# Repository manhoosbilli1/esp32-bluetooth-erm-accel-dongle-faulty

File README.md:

# daronjli_dongle_final_manufactured

ESP32 Bluetooth dongle with ERM haptic motor and accelerometer - FAULTY: wrong ORing circuit, used NMOS instead of PMOS

## At a Glance

- **Status**: Manufactured
- **Board size**: 23.26 x 28.39 mm
- **Layers**: 4
- **Components**: 56
- **Key ICs**:
  - U1: MCP73831-2-MC
  - U2: CP2102N-Axx-xQFN24
  - U3: LIS3DH
  - U4: DRV2605LDGS
  - U5: SY8089AAAC
  - U6: ESP32-WROOM-32E

## Schematic

Full PDF: [reports/schematic.pdf](reports/schematic.pdf)

## Component Roles

- **ESP32-WROVER-E** - main MCU with Bluetooth; firmware runs here
- **DRV2605LDGS** - haptic motor driver (configured for ERM motor) for tactile feedback
- **LIS3DH** - 3-axis accelerometer for orientation / motion detection
- **CP2102N** - USB-to-UART bridge for firmware programming
- **TPS63020** - buck-boost regulator (stable 3.3 V from a swinging LiPo)
- **MCP73871** - LiPo charger with PowerPath (USB vs battery source switching)
- **MAX17048** - I2C fuel gauge for battery percentage

## Known fault

This manufactured revision has a **broken OR-ing / PowerPath circuit**: the design used an N-channel MOSFET where a P-channel MOSFET was required. Result: source switching between USB and battery does not work correctly. Use the active [daronjli-dongle](https://github.com/manhoosbilli1/daronjli-dongle) repo for the fix.

## PCB

**Top copper**

**Bottom copper**

## Bill of Materials

| Refs | Value | Footprint | Qty | MPN | LCSC |
|------|-------|-----------|----:|-----|------|
| C1,C3,C7,C14-C16 | 100nF | Capacitor_SMD:C_0402_1005Metric | 6 |  |  |
| C2,C6 | 4.7uF | Capacitor_SMD:C_0402_1005Metric | 2 |  | [C307423](https://www.lcsc.com/product-detail/_C307423.html) |
| C4,C5 | 22uF | Capacitor_SMD:C_0402_1005Metric | 2 |  |  |
| C8,C10,C13 | 10uF | Capacitor_SMD:C_0402_1005Metric | 3 |  |  |
| C9,C12 | 1uF | Capacitor_SMD:C_0402_1005Metric | 2 |  |  |
| C11 | 22pF | Capacitor_SMD:C_0402_1005Metric | 1 |  |  |
| D1 | WS2812B | PCM_JLCPCB:LED_WS2812B_PLCC4_5.0x5.0mm_P3.2mm | 1 |  | [C22461793](https://www.lcsc.com/product-detail/_C22461793.html) |
| D2,D5,D6 | H5VL06B | PCM_JLCPCB:D_DFN0603-2L | 3 |  | [C7420373](https://www.lcsc.com/product-detail/_C7420373.html) |
| D3 | Red | PCM_JLCPCB:D_0603 | 1 |  | [C2286](https://www.lcsc.com/product-detail/_C2286.html) |
| D4 | B5819W | Diode_SMD:D_SOD-123 | 1 |  |  |
| L1 | 2.2uH | Inductor_SMD:L_1008_2520Metric_Pad1.43x2.20mm_HandSolder | 1 |  |  |
| Q1,Q2 | BC817 | Package_TO_SOT_SMD:SOT-23 | 2 |  |  |
| Q3 | DMG3414U | Package_TO_SOT_SMD:SOT-23 | 1 |  |  |
| R1-R3,R11,R14,R15 | 10k | Resistor_SMD:R_0402_1005Metric | 6 |  | [C60490](https://www.lcsc.com/product-detail/_C60490.html) |
| R4 | 1k | Resistor_SMD:R_0402_1005Metric | 1 |  | [C106235](https://www.lcsc.com/product-detail/_C106235.html) |
| R5,R13 | 5.1kΩ | PCM_JLCPCB:R_0402 | 2 |  | [C25905](https://www.lcsc.com/product-detail/_C25905.html) |
| R6-R8 | 2.2k | Resistor_SMD:R_0402_1005Metric | 3 |  |  |
| R9,R18 | 100k | Resistor_SMD:R_0402_1005Metric | 2 |  |  |
| R10 | 22.1k | Resistor_SMD:R_0402_1005Metric | 1 |  | [C43473](https://www.lcsc.com/product-detail/_C43473.html) |
| R12 | 10kΩ | PCM_JLCPCB:R_0402 | 1 |  | [C25744](https://www.lcsc.com/product-detail/_C25744.html) |
| R16 | 4.7kΩ | PCM_JLCPCB:R_0402 | 1 |  | [C25900](https://www.lcsc.com/product-detail/_C25900.html) |
| TP1-TP4 | TestPoint | TestPoint:TestPoint_Pad_3.0x3.0mm | 4 |  |  |
| TP5,TP6 | TestPoint | TestPoint:TestPoint_Pad_D1.0mm | 2 |  |  |
| U1 | MCP73831-2-MC | Package_DFN_QFN:DFN-8-1EP_3x2mm_P0.5mm_EP1.7x1.4mm | 1 |  | [C150772](https://www.lcsc.com/product-detail/_C150772.html) |
| U2 | CP2102N-Axx-xQFN24 | Package_DFN_QFN:QFN-24-1EP_4x4mm_P0.5mm_EP2.6x2.6mm | 1 |  | [C969151](https://www.lcsc.com/product-detail/_C969151.html) |
| U3 | LIS3DH | Package_LGA:LGA-16_3x3mm_P0.5mm_LayoutBorder3x5y | 1 |  |  |
| U4 | DRV2605LDGS | Package_SO:VSSOP-10_3x3mm_P0.5mm | 1 |  |  |
| U5 | SY8089AAAC | footprints:SY8089AAAC_SGY | 1 |  |  |
| U6 | ESP32-WROOM-32E | RF_Module:ESP32-WROOM-32D | 1 |  | [C701343](https://www.lcsc.com/product-detail/_C701343.html) |
| USB1 | HX-TYPE-C 16P 180 LC-B H10.0 TYPE C VERTICAL | :USB-C-TH_HX-TYPE-C-16P-180-LC-BH10.0-TYPE-C-VERTICAL | 1 |  |  |

_17 of 30 line items don't have an LCSC code in the schematic - search [LCSC](https://www.lcsc.com/) or [JLC parts search](https://jlcsearch.tscircuit.com/) by MPN or footprint when sourcing._

## Files

- `daronjli_dongle.kicad_pro` - KiCad project
- `daronjli_dongle.kicad_sch` - schematic source
- `daronjli_dongle.kicad_pcb` - PCB layout source
- `reports/schematic.pdf` - full schematic (printable)
- `reports/bom.csv` - bill of materials
- `reports/pcb-top.svg`, `reports/pcb-bottom.svg` - copper artwork
- `reports/board-stats.json` - KiCad-generated board statistics

---

_Renders and metadata auto-generated by `Backup-KiCadProject.ps1` using KiCad 10.0._

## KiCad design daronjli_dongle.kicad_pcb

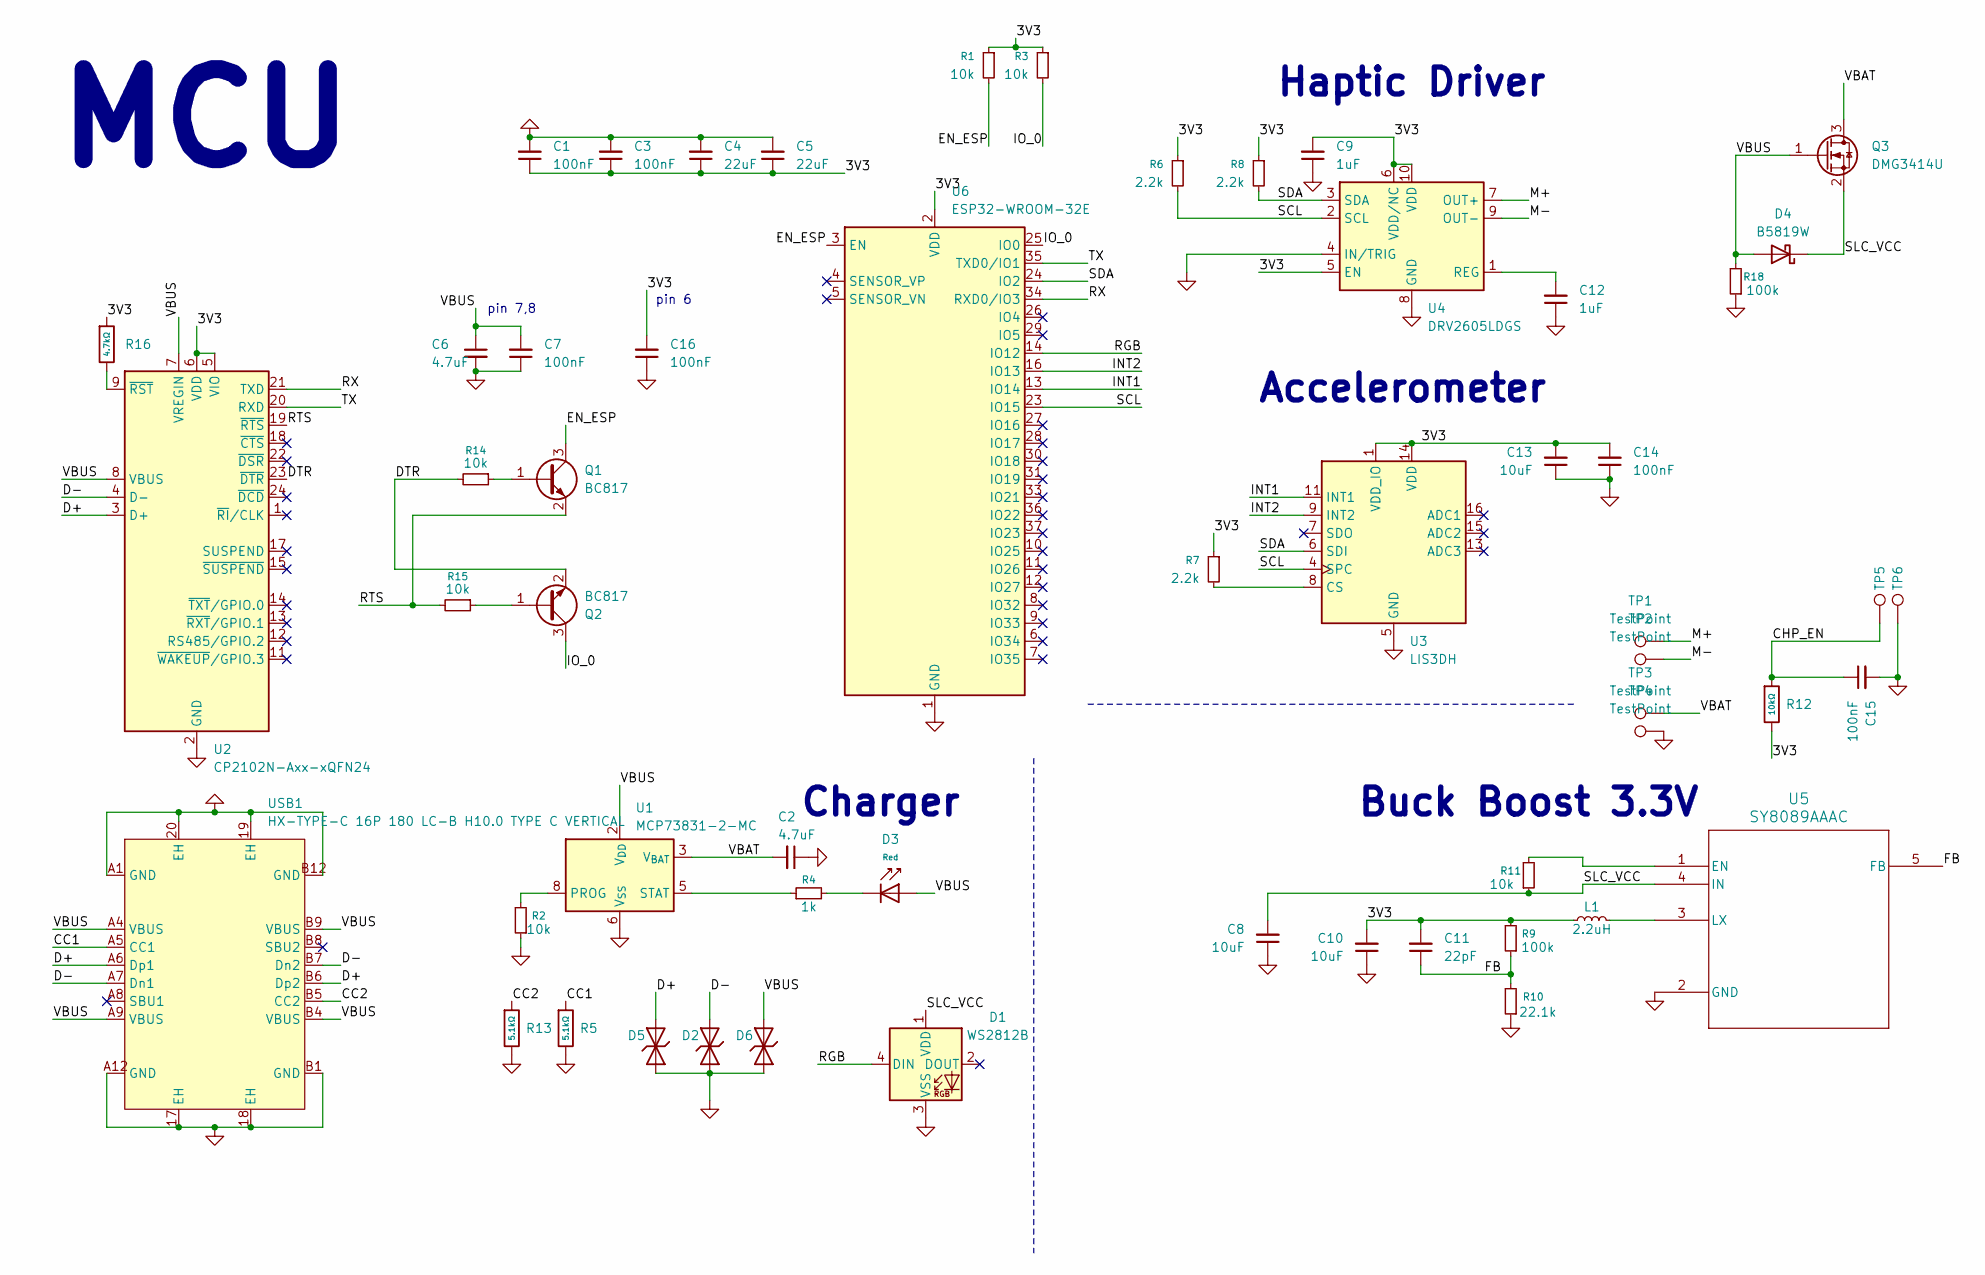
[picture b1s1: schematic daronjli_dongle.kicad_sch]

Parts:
C1, C3, C7, C14, C15, C16: 100nF; C_0402_1005Metric
C2, C6: 4.7uF; C_0402_1005Metric; LCSC C307423
C4, C5: 22uF; C_0402_1005Metric
C8, C10, C13: 10uF; C_0402_1005Metric
C9, C12: 1uF; C_0402_1005Metric
C11: 22pF; C_0402_1005Metric
D1: WS2812B; LED_WS2812B_PLCC4_5.0x5.0mm_P3.2mm; LCSC C22461793
D2, D5, D6: H5VL06B; D_DFN0603-2L; Clamping Voltage@Ipp 10V; Breakdown Voltage (VBR) 5.6V; Part H5VL06B; LCSC C7420373
D3: Red; D_0603; Part KT-0603R; LCSC C2286
D4: B5819W; D_SOD-123
L1: 2.2uH; L_1008_2520Metric_Pad1.43x2.20mm_HandSolder
Q1, Q2: BC817; SOT-23
Q3: DMG3414U; SOT-23
R1, R3, R11, R14, R15: 10k; R_0402_1005Metric
R2: 10k; R_0402_1005Metric; LCSC C60490
R4: 1k; R_0402_1005Metric; LCSC C106235
R5, R13: 5.1kΩ; R_0402; Overload Voltage (Max) 50V; Tolerance ±1%; Part 0402WGF5101TCE; LCSC C25905
R6, R7, R8: 2.2k; R_0402_1005Metric
R9, R18: 100k; R_0402_1005Metric
R10: 22.1k; R_0402_1005Metric; LCSC C43473
R12: 10kΩ; R_0402; Overload Voltage (Max) 50V; Tolerance ±1%; Part 0402WGF1002TCE; LCSC C25744
R16: 4.7kΩ; R_0402; Overload Voltage (Max) 50V; Tolerance ±1%; Part 0402WGF4701TCE; LCSC C25900
TP1, TP2, TP3, TP4: TestPoint; TestPoint_Pad_3.0x3.0mm
TP5, TP6: TestPoint; TestPoint_Pad_D1.0mm
U1: MCP73831-2-MC; DFN-8-1EP_3x2mm_P0.5mm_EP1.7x1.4mm; LCSC C150772
U2: CP2102N-Axx-xQFN24; QFN-24-1EP_4x4mm_P0.5mm_EP2.6x2.6mm; LCSC C969151
U3: LIS3DH; LGA-16_3x3mm_P0.5mm_LayoutBorder3x5y
U4: DRV2605LDGS; VSSOP-10_3x3mm_P0.5mm
U5: SY8089AAAC; SY8089AAAC_SGY
U6: ESP32-WROOM-32E; ESP32-WROOM-32D; LCSC C701343
USB1: HX-TYPE-C 16P 180 LC-B H10.0 TYPE C VERTICAL; USB-C-TH_HX-TYPE-C-16P-180-LC-BH10.0-TYPE-C-VERTICAL; LCSC Part C49261584

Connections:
/3V3: C1.1, C3.1, C4.1, C5.1, C9.2, C10.2, C11.2, C13.2, C14.2, C16.2, L1.1, R1.1, R3.1, R6.1, R7.1, R8.1, R9.2, R12.2, R16.1, U2.5 (VIO), U2.6 (VDD), U3.1 (VDD_IO), U3.14 (VDD), U4.5 (EN), U4.6 (VDD/NC), U4.10 (VDD), U6.2 (VDD)
/CC1: R5.1, USB1.A5 (CC1)
/CC2: R13.1, USB1.B5 (CC2)
/CHP_EN: C15.1, R12.1, TP5.1
/D+: D5.2, U2.3 (D+), USB1.A6 (Dp1), USB1.B6 (Dp2)
/D-: D2.2, U2.4 (D-), USB1.A7 (Dn1), USB1.B7 (Dn2)
/DTR: Q2.2 (E), R14.2, U2.23 (~DTR)
/EN_ESP: Q1.3 (C), R1.2, U6.3 (EN)
/FB: C11.1, R9.1, R10.2, U5.5 (FB)
/INT1: U3.11 (INT1), U6.13 (IO14)
/INT2: U3.9 (INT2), U6.16 (IO13)
/IO_0: Q2.3 (C), R3.2, U6.25 (IO0)
/M+: TP1.1, U4.7 (OUT+)
/M-: TP2.1, U4.9 (OUT-)
/RGB: D1.4 (DIN), U6.14 (IO12)
/RTS: Q1.2 (E), R15.2, U2.19 (~RTS)
/RX: U2.21 (TXD), U6.34 (RXD0/IO3)
/SCL: R6.2, U3.4 (SPC), U4.2 (SCL), U6.23 (IO15)
/SDA: R8.2, U3.6 (SDI), U4.3 (SDA), U6.24 (IO2)
/SLC_VCC: C8.2, D1.1 (VDD), D4.1 (K), Q3.2 (S), R11.1, U5.4 (IN)
/TX: U2.20 (RXD), U6.35 (TXD0/IO1)
/VBAT: C2.2, Q3.3 (D), TP3.1, U1.3 (V_{BAT}), U1.4 (V_{BAT})
/VBUS: C6.1, C7.2, D3.2, D4.2 (A), D6.2, Q3.1 (G), R18.2, U1.1 (V_{DD}), U1.2 (V_{DD}), U2.7 (VREGIN), U2.8 (VBUS), USB1.A4 (VBUS), USB1.A9 (VBUS), USB1.B4 (VBUS), USB1.B9 (VBUS)
GND: C1.2, C2.1, C3.2, C4.2, C5.2, C6.2, C7.1, C8.1, C9.1, C10.1, C12.1, C13.1, C14.1, C15.2, C16.1, D1.3 (VSS), D2.1, D5.1, D6.1, R2.1, R5.2, R10.1, R13.2, R18.1, TP4.1, TP6.1, U1.6 (V_{SS}), U2.2 (GND), U2.25 (GND), U3.5 (GND), U3.10 (GND), U3.12 (GND), U4.4 (IN/TRIG), U4.8 (GND), U5.2 (GND), U6.1 (GND), U6.15 (GND), U6.38 (GND), U6.39 (GND), USB1.17 (EH), USB1.18 (EH), USB1.19 (EH), USB1.20 (EH), USB1.A1 (GND), USB1.A12 (GND), USB1.B1 (GND), USB1.B12 (GND)
unnamed: D3.1, R4.2
unnamed: Q1.1 (B), R14.1
unnamed: Q2.1 (B), R15.1
unnamed: R2.2, U1.8 (PROG)
unnamed: R4.1, U1.5 (STAT)
unnamed: R16.2, U2.9 (~RST)
unnamed: R7.2, U3.8 (CS)
unnamed: C12.2, U4.1 (REG)
unnamed: R11.2, U5.1 (EN)
unnamed: L1.2, U5.3 (LX)

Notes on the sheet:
pin 7,8
pin 6
MCU
Buck Boost 3.3V
Haptic Driver
Accelerometer
Charger

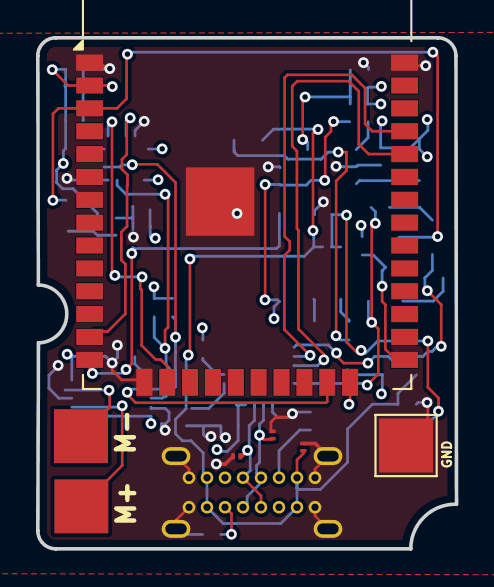
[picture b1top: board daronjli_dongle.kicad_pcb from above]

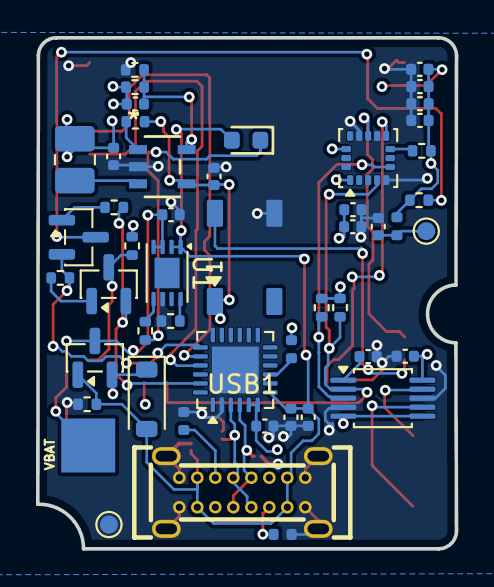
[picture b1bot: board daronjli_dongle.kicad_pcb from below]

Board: 4 copper layers, 23.3 x 28.4 mm, 56 parts (49 on the bottom side), 34 nets.

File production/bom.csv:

Designator,Footprint,Quantity,Value,LCSC Part #
"C1, C14, C15, C16, C3, C7",0402,6,100nF,
"C10, C13, C8",0402,3,10uF,
C11,0402,1,22pF,
"C12, C9",0402,2,1uF,
"C2, C6",0402,2,4.7uF,C307423
"C4, C5",0402,2,22uF,
D1,LED_WS2812B_PLCC4_5.0x5.0mm_P3.2mm,1,WS2812B,C22461793
"D2, D5, D6",D_DFN0603-2L,3,H5VL06B,C7420373
D3,D_0603,1,Red,C2286
D4,D_SOD-123,1,B5819W,
L1,1008,1,2.2uH,
"Q1, Q2",SOT-23,2,BC817,
Q3,SOT-23,1,DMG3414U,
"R1, R11, R14, R15, R3",0402,5,10k,
R10,0402,1,22.1k,C43473
R12,R_0402,1,10kΩ,C25744
"R13, R5",R_0402,2,5.1kΩ,C25905
R16,R_0402,1,4.7kΩ,C25900
"R18, R9",0402,2,100k,
R2,0402,1,10k,C60490
R4,0402,1,1k,C106235
"R6, R7, R8",0402,3,2.2k,
"TP1, TP2, TP3, TP4",TestPoint_Pad_3.0x3.0mm,4,TestPoint,
"TP5, TP6",TestPoint_Pad_D1.0mm,2,TestPoint,
U1,DFN-8-1EP_3x2mm_P0.5mm_EP1.7x1.4mm,1,MCP73831-2-MC,C150772
U2,QFN-24-1EP_4x4mm_P0.5mm_EP2.6x2.6mm,1,CP2102N-Axx-xQFN24,C969151
U3,LGA-16_3x3mm_P0.5mm_LayoutBorder3x5y,1,LIS3DH,
U4,VSSOP-10_3x3mm_P0.5mm,1,DRV2605LDGS,
U5,SY8089AAAC_SGY,1,SY8089AAAC,
U6,ESP32-WROOM-32D,1,ESP32-WROOM-32E,C701343
USB1,USB-C-TH_HX-TYPE-C-16P-180-LC-BH10.0-TYPE-C-VERTICAL,1,HX-TYPE-C 16P 180 LC-B H10.0 TYPE C VERTICAL,C49261584

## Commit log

2026-05-18 Initial backup: schematic, PCB, renders, BOM
2026-05-18 Enrich README: schematic PNG, component roles, BOM table
